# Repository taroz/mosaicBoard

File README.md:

# mosaic-Board
## Introduction
- **mosaic-Board** = [**mosaic**](https://github.com/septentrio-gnss/mosaicHAT) + **micro SD card** + **Ethernet** + **Case**
- We use [Septentrio's mosaic-X5](https://www.septentrio.com/en/products/gnss-receivers/rover-base-receivers/receivers-module/mosaic) GNSS module which is a **low-cost** and **survey-grade** GNSS receiver
- This project is inspired by [mosaicHAT](https://github.com/septentrio-gnss/mosaicHAT) and extends it further. Thanks to the wonderful project [mosaicHAT](https://github.com/septentrio-gnss/mosaicHAT)!
- License: [Creative Commons Attribution Share-Alike License](https://creativecommons.org/licenses/by-sa/4.0/). and [Open Source HW](https://www.oshwa.org/definition/)  

## Features
- The mosaic-Board has a RJ45 LAN connector and can easily distribute GNSS reference station data over the Internet without a PC by using mosaic's built-in Ntrip Caster or Ntrip Server.
- The micro SD card enables use as a GNSS logger without a PC.

## Board
- The design of the board is based on the original [mosaicHAT](https://github.com/septentrio-gnss/mosaicHAT).
  - RJ45 connector has been added
  - Micro SD card and log button have been added for data logging capability
- [KiCAD files](./board/KiCAD) and [gerber](./board/gerber)
- Bill of Materials (BOM) is [here](./board/BOM.xlsx)                                 

## Case
- Metal case design data (Fusion 360, STEP) is [available](./case)

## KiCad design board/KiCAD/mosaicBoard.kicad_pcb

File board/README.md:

# mosaic-Board Design Files
- We used KiCAD 6 for our design. [KiCAD 6 or later](https://www.kicad.org/) must be installed in order to edit the design data.
- BOM
  - `BOM.xlsx` shows the parts to be used and where to obtain them.

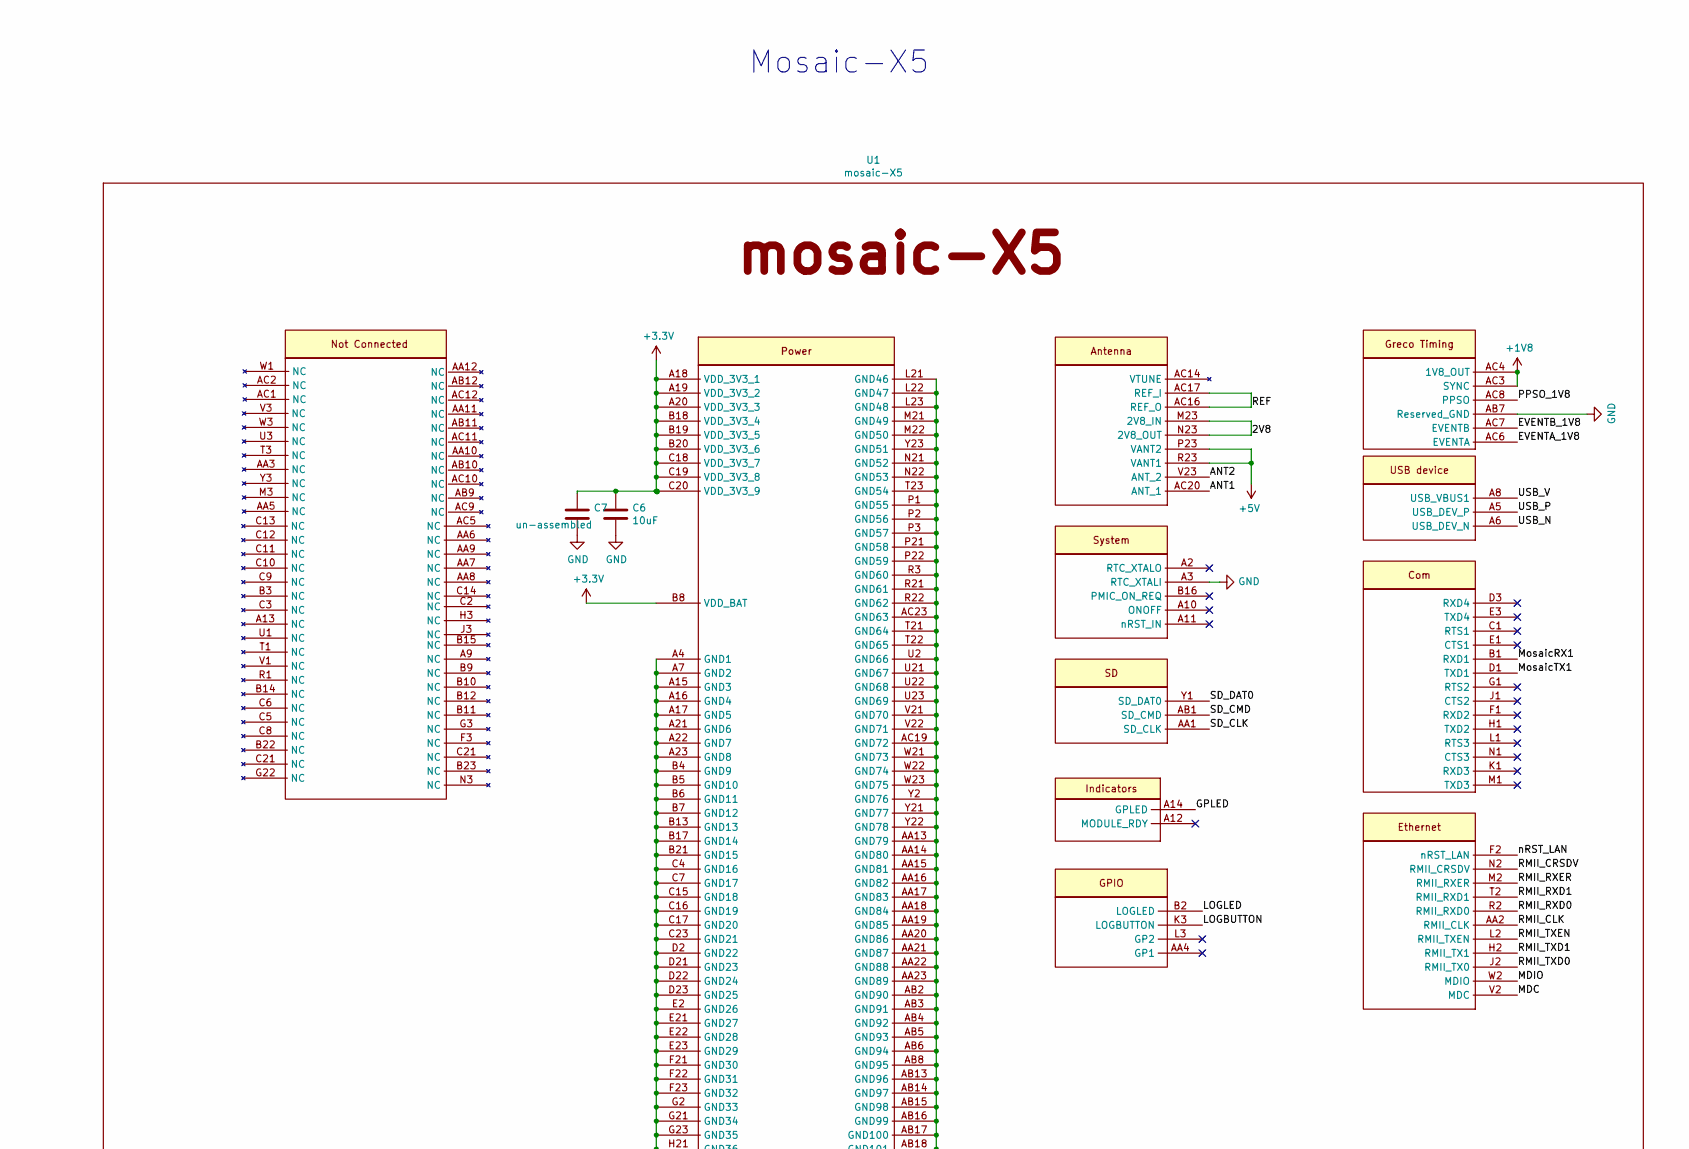
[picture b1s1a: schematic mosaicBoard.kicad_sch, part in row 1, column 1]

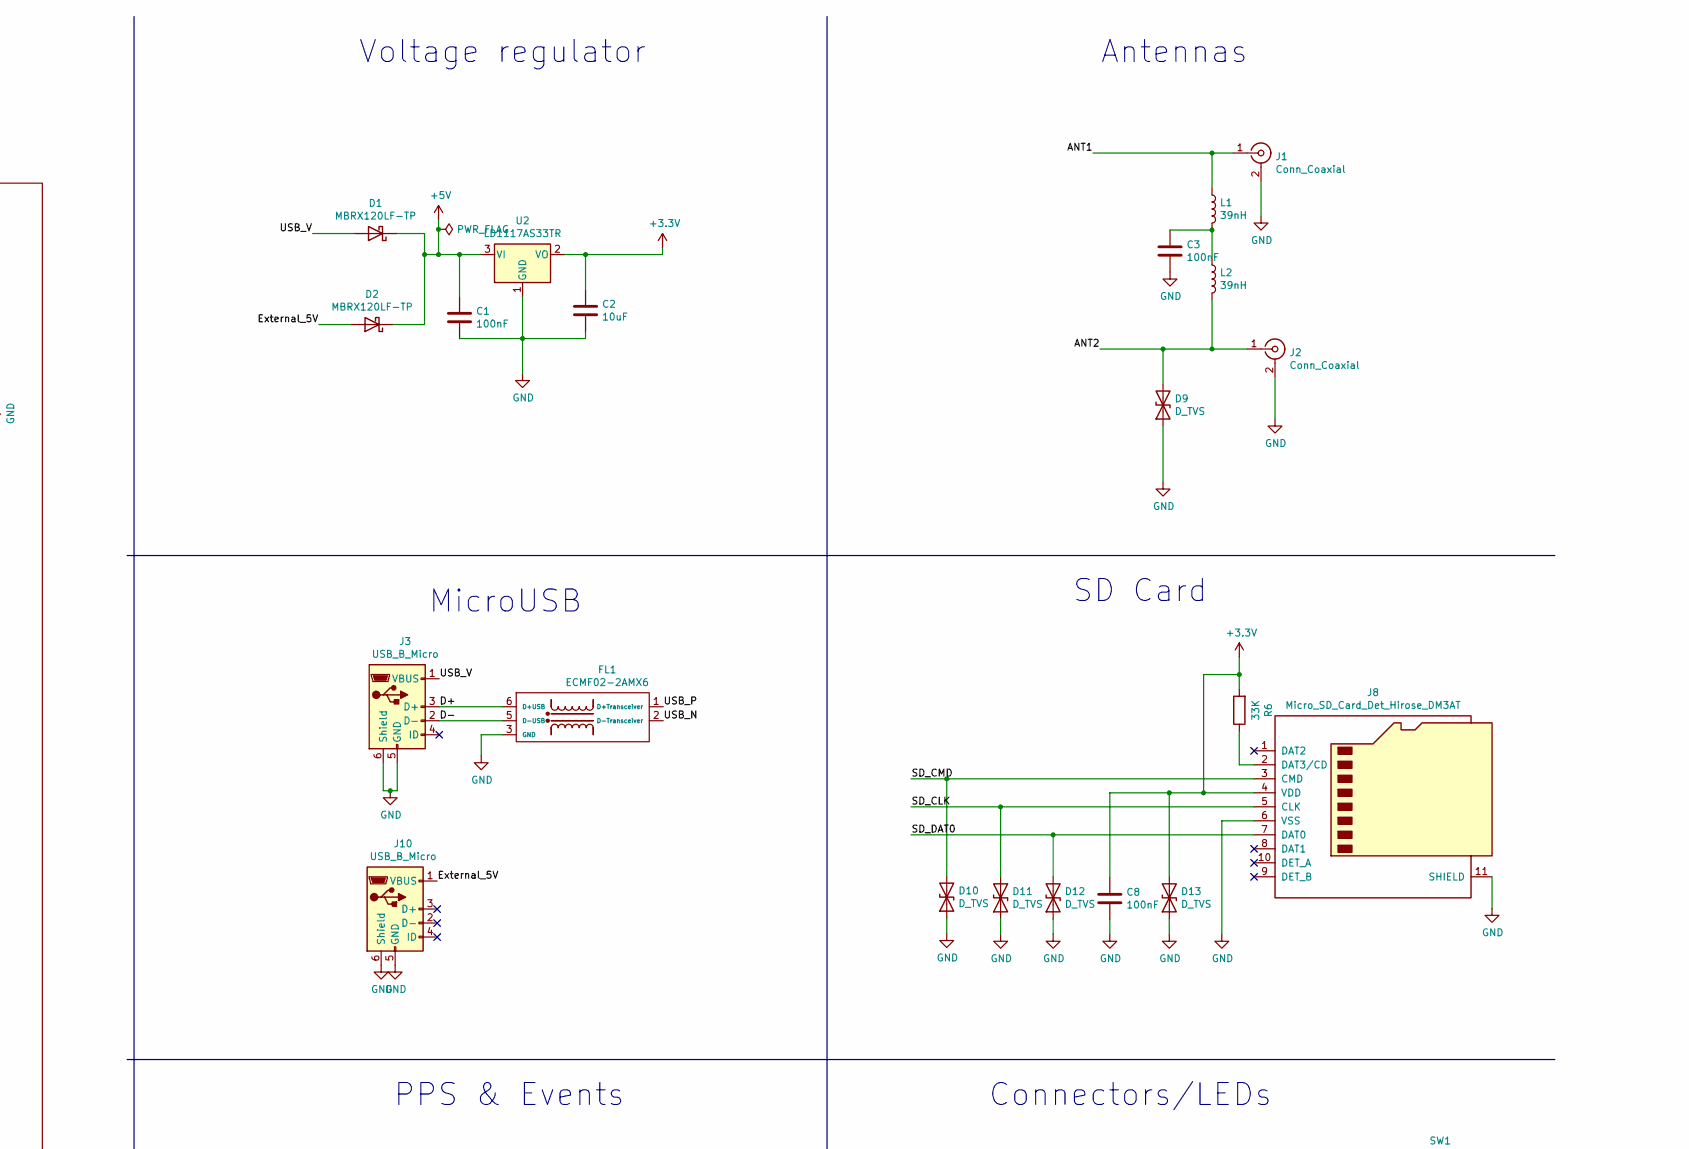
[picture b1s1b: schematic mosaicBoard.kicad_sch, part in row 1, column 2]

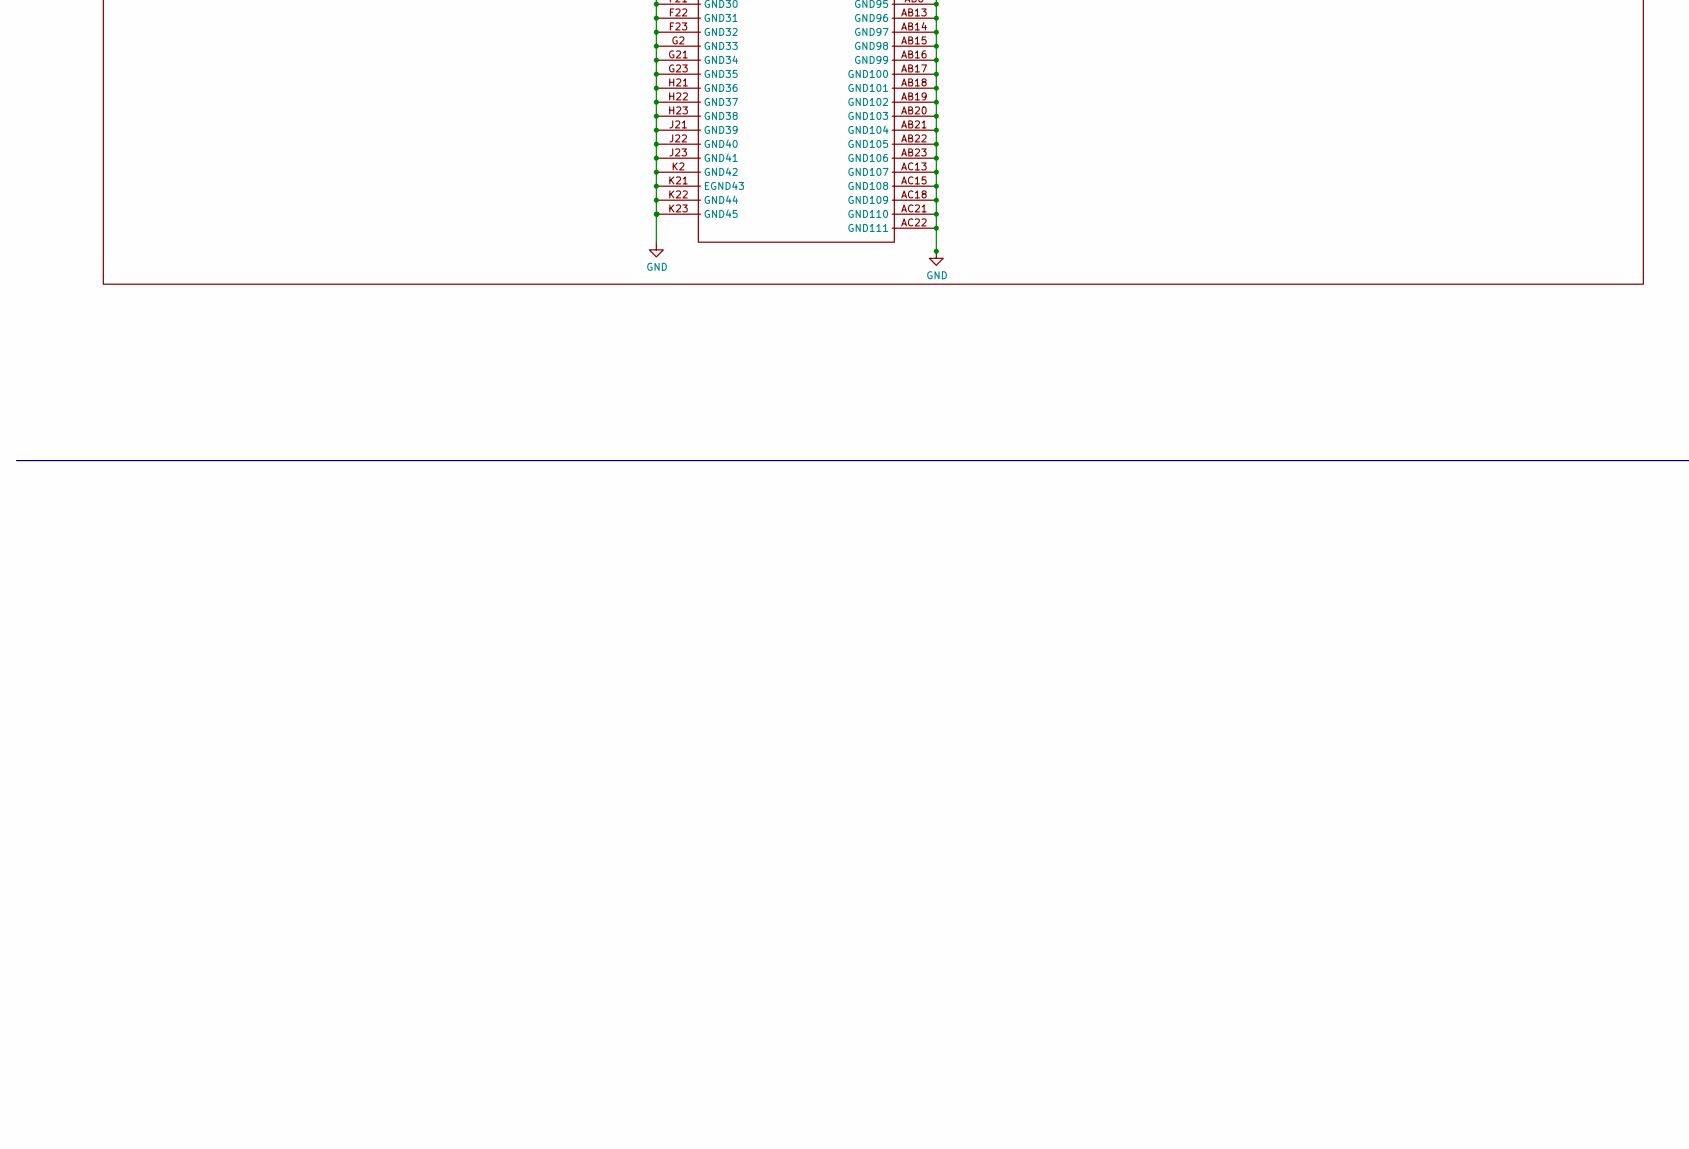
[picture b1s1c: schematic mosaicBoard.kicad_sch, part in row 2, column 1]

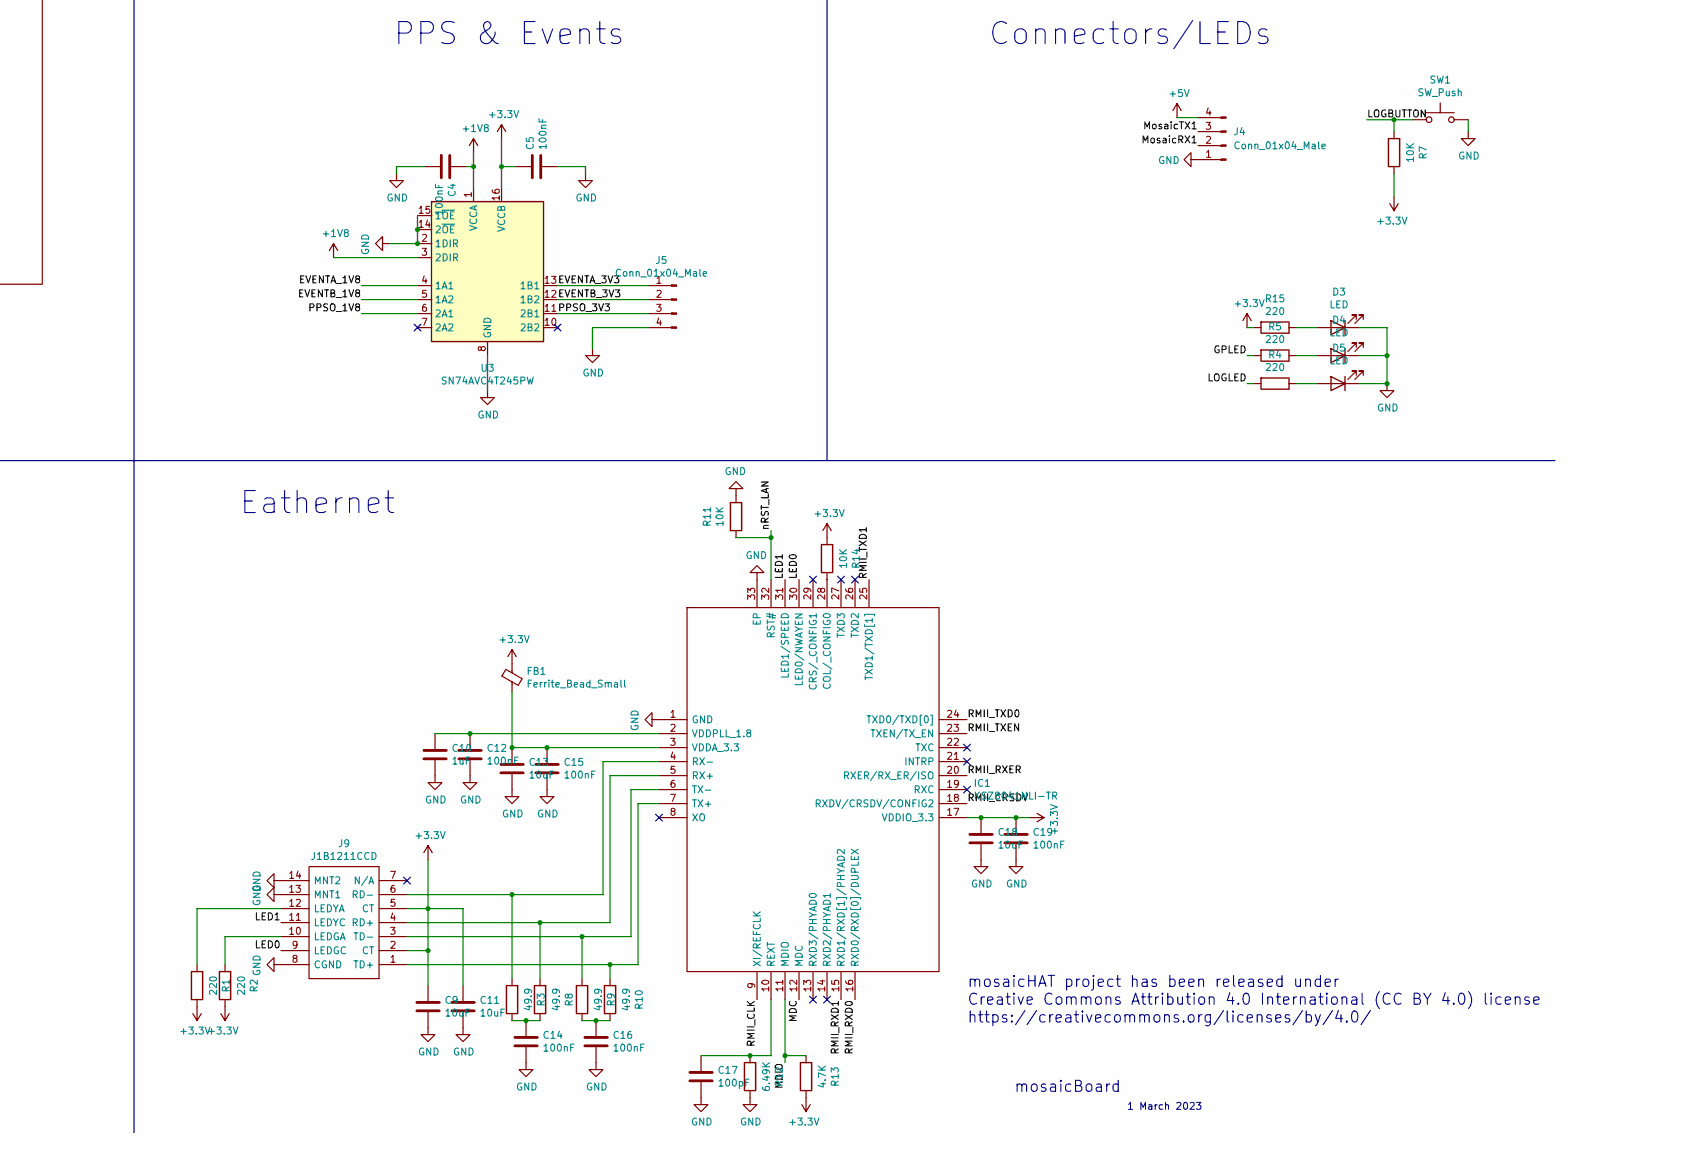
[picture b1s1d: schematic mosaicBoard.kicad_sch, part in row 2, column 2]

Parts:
C1, C3, C4, C5, C8, C12, C14, C15, C16, C19: 100nF; C_0603_1608Metric
C2, C6, C9, C11, C13, C18: 10uF; C_0603_1608Metric
C7: un-assembled; C_0603_1608Metric
C10: 1uF; C_0603_1608Metric
C17: 100pF; C_0603_1608Metric
D1, D2: MBRX120LF-TP; D_SOD-123
D3: LED; LED_D1.8mm_W1.8mm_H2.4mm_Horizontal_O1.27mm_Z1.6mm
D4: LED; LED_D1.8mm_W1.8mm_H2.4mm_Horizontal_O3.81mm_Z4.9mm
D5: LED; LED_D1.8mm_W1.8mm_H2.4mm_Horizontal_O6.35mm_Z8.2mm
D9, D10, D11, D12, D13: D_TVS; R_0402_1005Metric
FB1: Ferrite_Bead_Small; L_0603_1608Metric
FL1: ECMF02-2AMX6; ST_UQFN-6L_1.5x1.7mm_Pitch0.5mm
IC1: KSZ8041NLI-TR; QFN50P500X500X90-33N-D; Mouser Part Number 998-KSZ8041NLITR
J1, J2: Conn_Coaxial; SMA_Amphenol_132203-12_Horizontal_mod
J3, J10: USB_B_Micro; USB_Micro-B_Molex-105017-0001
J4, J5: Conn_01x04_Male; PinHeader_1x04_P2.54mm_Vertical
J8: Micro_SD_Card_Det_Hirose_DM3AT; microSD_HC_Hirose_DM3AT-SF-PEJM5
J9: J1B1211CCD; Mouser Part Number 950-J1B1211CCD
L1, L2: 39nH; L_0603_1608Metric
R1, R2, R4, R5, R15: 220; R_0603_1608Metric
R3, R8, R9, R10: 49.9; R_0603_1608Metric
R6: 33K; R_0603_1608Metric
R7, R11, R14: 10K; R_0603_1608Metric
R12: 6.49K; R_0603_1608Metric
R13: 4.7K; R_0603_1608Metric
SW1: SW_Push; SW_Tactile_SKHH_Angled
U1: mosaic-X5; mosaic_X5
U2: LD1117AS33TR; SOT-223
U3: SN74AVC4T245PW; TSSOP-16_4.4x5mm_P0.65mm

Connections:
+1V8: C4.1, U1.AC3 (SYNC), U1.AC4 (1V8_OUT), U3.1 (VCCA), U3.3 (2DIR)
+3.3V: C2.1, C5.1, C6.1, C7.1, C8.1, C9.1, C11.1, C18.1, C19.1, D13.2 (A2), FB1.1, IC1.17 (VDDIO_3.3), J8.4 (VDD), J9.2 (CT), J9.5 (CT), R1.1, R2.1, R6.2, R7.1, R13.1, R14.2, R15.2, U1.A18 (VDD_3V3_1), U1.A19 (VDD_3V3_2), U1.A20 (VDD_3V3_3), U1.B8 (VDD_BAT), U1.B18 (VDD_3V3_4), U1.B19 (VDD_3V3_5), U1.B20 (VDD_3V3_6), U1.C18 (VDD_3V3_7), U1.C19 (VDD_3V3_8), U1.C20 (VDD_3V3_9), U2.2 (VO), U3.16 (VCCB)
+5V: C1.1, D1.1 (K), D2.1 (K), J4.4, U1.P23 (VANT2), U1.R23 (VANT1), U2.3 (VI)
/2V8: U1.M23 (2V8_IN), U1.N23 (2V8_OUT)
/ANT1: J1.1 (In), L1.1, U1.AC20 (ANT_1)
/ANT2: D9.2 (A2), J2.1 (In), L2.2, U1.V23 (ANT_2)
/D+: FL1.6 (D+USB), J3.3 (D+)
/D-: FL1.5 (D-USB), J3.2 (D-)
/EVENTA_1V8: U1.AC6 (EVENTA), U3.4 (1A1)
/EVENTA_3V3: J5.1, U3.13 (1B1)
/EVENTB_1V8: U1.AC7 (EVENTB), U3.5 (1A2)
/EVENTB_3V3: J5.2, U3.12 (1B2)
/External_5V: D2.2 (A), J10.1 (VBUS)
/GPLED: R5.2, U1.A14 (GPLED)
/LED0: IC1.30 (LED0/NWAYEN), J9.9 (LEDGC)
/LED1: IC1.31 (LED1/SPEED), J9.11 (LEDYC)
/LOGBUTTON: R7.2, SW1.1, U1.K3 (LOGBUTTON)
/LOGLED: R4.2, U1.B2 (LOGLED)
/MDC: IC1.12 (MDC), U1.V2 (MDC)
/MDIO: IC1.11 (MDIO), R13.2, U1.W2 (MDIO)
/MosaicRX1: J4.2, U1.B1 (RXD1)
/MosaicTX1: J4.3, U1.D1 (TXD1)
/PPSO_1V8: U1.AC8 (PPSO), U3.6 (2A1)
/PPSO_3V3: J5.3, U3.11 (2B1)
/REF: U1.AC16 (REF_O), U1.AC17 (REF_I)
/RMII_CLK: IC1.9 (XI/REFCLK), U1.AA2 (RMII_CLK)
/RMII_CRSDV: IC1.18 (RXDV/CRSDV/CONFIG2), U1.N2 (RMII_CRSDV)
/RMII_RXD0: IC1.16 (RXD0/RXD[0]/DUPLEX), U1.R2 (RMII_RXD0)
/RMII_RXD1: IC1.15 (RXD1/RXD[1]/PHYAD2), U1.T2 (RMII_RXD1)
/RMII_RXER: IC1.20 (RXER/RX_ER/ISO), U1.M2 (RMII_RXER)
/RMII_TXD0: IC1.24 (TXD0/TXD[0]), U1.J2 (RMII_TX0)
/RMII_TXD1: IC1.25 (TXD1/TXD[1]), U1.H2 (RMII_TX1)
/RMII_TXEN: IC1.23 (TXEN/TX_EN), U1.L2 (RMII_TXEN)
/SD_CLK: D11.2 (A2), J8.5 (CLK), U1.AA1 (SD_CLK)
/SD_CMD: D10.2 (A2), J8.3 (CMD), U1.AB1 (SD_CMD)
/SD_DAT0: D12.2 (A2), J8.7 (DAT0), U1.Y1 (SD_DAT0)
/USB_N: FL1.2 (D-Transceiver), U1.A6 (USB_DEV_N)
/USB_P: FL1.1 (D+Transceiver), U1.A5 (USB_DEV_P)
/USB_V: D1.2 (A), J3.1 (VBUS), U1.A8 (USB_VBUS1)
/nRST_LAN: IC1.32 (RST#), R11.2, U1.F2 (nRST_LAN)
GND: C1.2, C2.2, C3.2, C4.2, C5.2, C6.2, C7.2, C8.2, C9.2, C10.2, C11.2, C12.2, C13.2, C14.2, C15.2, C16.2, C17.2, C18.2, C19.2, D3.1 (K), D4.1 (K), D5.1 (K), D9.1 (A1), D10.1 (A1), D11.1 (A1), D12.1 (A1), D13.1 (A1), FL1.3 (GND), IC1.1 (GND), IC1.33 (EP), J1.2 (Ext), J2.2 (Ext), J3.5 (GND), J3.6 (Shield), J4.1, J5.4, J8.6 (VSS), J8.11 (SHIELD), J9.8 (CGND), J9.13 (MNT1), J9.14 (MNT2), J10.5 (GND), J10.6 (Shield), R11.1, R12.1, SW1.2, U1.A3 (RTC_XTALI), U1.A4 (GND1), U1.A7 (GND2), U1.A15 (GND3), U1.A16 (GND4), U1.A17 (GND5), U1.A21 (GND6), U1.A22 (GND7), U1.A23 (GND8), U1.AA13 (GND79), U1.AA14 (GND80), U1.AA15 (GND81), U1.AA16 (GND82), U1.AA17 (GND83), U1.AA18 (GND84), U1.AA19 (GND85), U1.AA20 (GND86), U1.AA21 (GND87), U1.AA22 (GND88), U1.AA23 (GND89), U1.AB2 (GND90), U1.AB3 (GND91), U1.AB4 (GND92), U1.AB5 (GND93), U1.AB6 (GND94), U1.AB7 (Reserved_GND), U1.AB8 (GND95), U1.AB13 (GND96), U1.AB14 (GND97), U1.AB15 (GND98), U1.AB16 (GND99), U1.AB17 (GND100), U1.AB18 (GND101), U1.AB19 (GND102), U1.AB20 (GND103), U1.AB21 (GND104), U1.AB22 (GND105), U1.AB23 (GND106), U1.AC13 (GND107), U1.AC15 (GND108), U1.AC18 (GND109), U1.AC19 (GND72), U1.AC21 (GND110), U1.AC22 (GND111), U1.AC23 (GND63), U1.B4 (GND9), U1.B5 (GND10), U1.B6 (GND11), U1.B7 (GND12), U1.B13 (GND13), U1.B17 (GND14), U1.B21 (GND15), U1.C4 (GND16), U1.C7 (GND17), U1.C15 (GND18), U1.C16 (GND19), U1.C17 (GND20), U1.C23 (GND21), U1.D2 (GND22), U1.D21 (GND23), U1.D22 (GND24), U1.D23 (GND25), U1.E2 (GND26), U1.E21 (GND27), U1.E22 (GND28), U1.E23 (GND29), U1.F21 (GND30), U1.F22 (GND31), U1.F23 (GND32), U1.G2 (GND33), U1.G21 (GND34), U1.G23 (GND35), U1.H21 (GND36), U1.H22 (GND37), U1.H23 (GND38), U1.J21 (GND39), U1.J22 (GND40), U1.J23 (GND41), U1.K2 (GND42), U1.K21 (EGND43), U1.K22 (GND44), U1.K23 (GND45), U1.L21 (GND46), U1.L22 (GND47), U1.L23 (GND48), U1.M21 (GND49), U1.M22 (GND50), U1.N21 (GND52), U1.N22 (GND53), U1.P1 (GND55), U1.P2 (GND56), U1.P3 (GND57), U1.P21 (GND58), U1.P22 (GND59), U1.R3 (GND60), U1.R21 (GND61), U1.R22 (GND62), U1.T21 (GND64), U1.T22 (GND65), U1.T23 (GND54), U1.U2 (GND66), U1.U21 (GND67), U1.U22 (GND68), U1.U23 (GND69), U1.V21 (GND70), U1.V22 (GND71), U1.W21 (GND73), U1.W22 (GND74), U1.W23 (GND75), U1.Y2 (GND76), U1.Y21 (GND77), U1.Y22 (GND78), U1.Y23 (GND51), U2.1 (GND), U3.2 (1DIR), U3.8 (GND), U3.9 (GND), U3.14 (2~OE), U3.15 (1~OE)
unnamed: C3.1, L1.2, L2.1
unnamed: C10.1, C12.1, IC1.2 (VDDPLL_1.8)
unnamed: C13.1, C15.1, FB1.2, IC1.3 (VDDA_3.3)
unnamed: C14.1, R3.1, R8.1
unnamed: C16.1, R9.1, R10.1
unnamed: C17.1, IC1.10 (REXT), R12.2
unnamed: D3.2 (A), R15.1
unnamed: D4.2 (A), R5.1
unnamed: D5.2 (A), R4.1
unnamed: IC1.4 (RX-), J9.6 (RD-), R3.2
unnamed: IC1.5 (RX+), J9.4 (RD+), R8.2
unnamed: IC1.6 (TX-), J9.3 (TD-), R9.2
unnamed: IC1.7 (TX+), J9.1 (TD+), R10.2
unnamed: IC1.28 (COL/_CONFIG0), R14.1
unnamed: J8.2 (DAT3/CD), R6.1
unnamed: J9.10 (LEDGA), R2.2
unnamed: J9.12 (LEDYA), R1.2

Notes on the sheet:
mosaicHAT project has been released under Creative Commons Attribution 4.0 International (CC BY 4.0) license https://creativecommons.org/licenses/by/4.0/
SD Card
1 March 2023
Eathernet
Voltage regulator
PPS & Events
Mosaic-X5
Antennas
mosaicBoard
Connectors/LEDs
MicroUSB

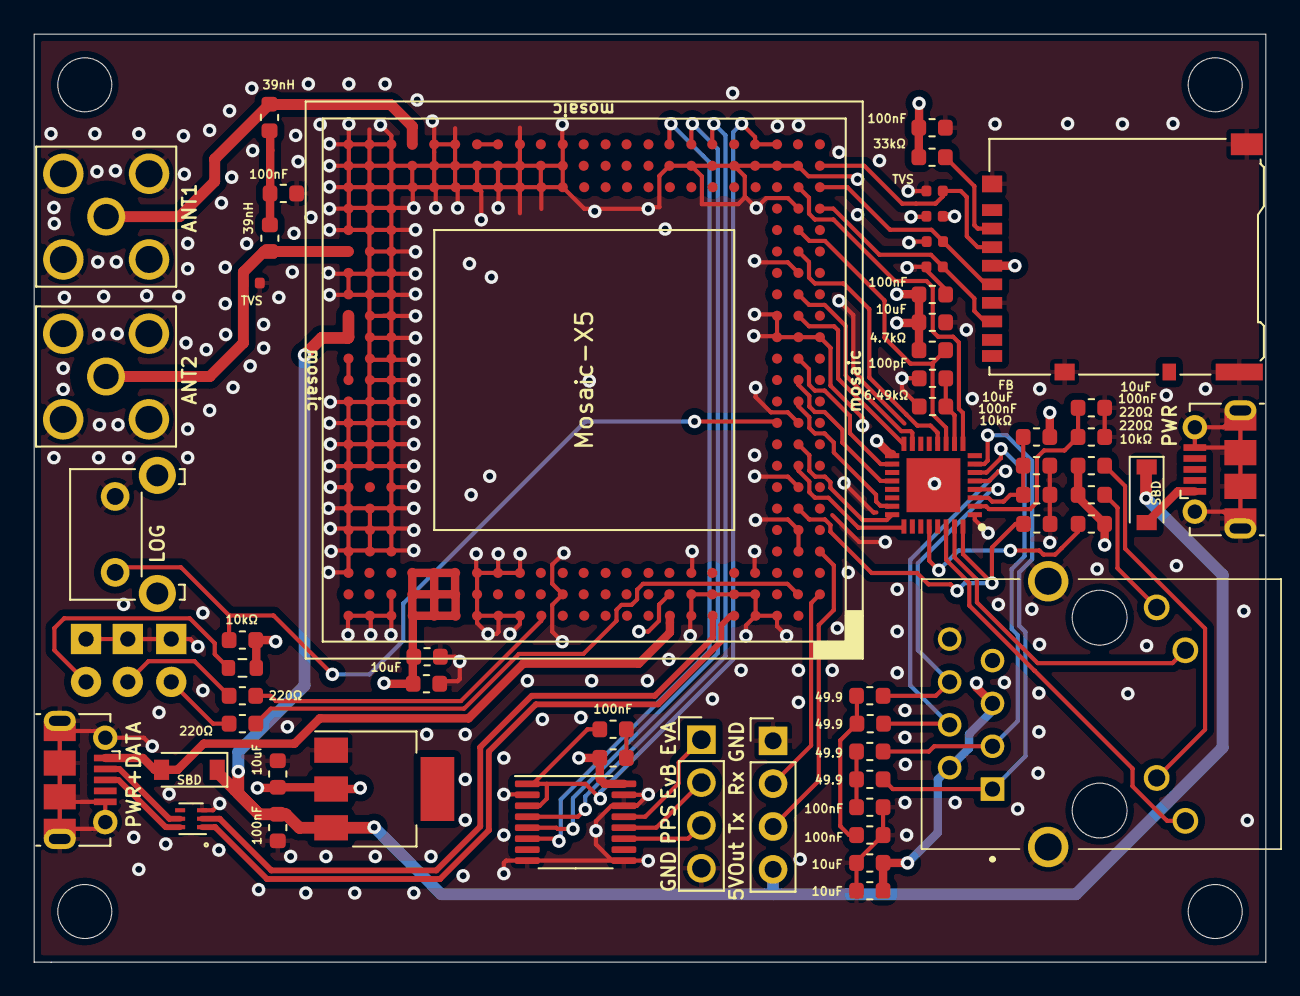
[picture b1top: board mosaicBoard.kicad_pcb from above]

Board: 4 copper layers, 73.0 x 55.0 mm, 61 parts (0 on the bottom side), 58 nets.

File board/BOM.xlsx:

Designator | Footprint | Quantity | Value | MPN
C1, C12, C14, C15, C16, C19, C3, C4, C5, C8 | C_0603_1608Metric | 10 | 100nF
C10 | C_0603_1608Metric | 1 | 1uF
C11, C13, C18, C2, C6, C9 | C_0603_1608Metric | 6 | 10uF
C17 | C_0603_1608Metric | 1 | 100pF
C7 | C_0603_1608Metric | 1 | un-assembled
D1, D2 | D_SOD-123 | 2 | MBRX120LF-TP | MBRX120LF-TP | https://www.digikey.com/product-detail/en/micro-commercial-c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
D10, D11, D12, D13, D9 | R_0402_1005Metric | 5 | D_TVS | SESD0402X1BN-0010-098 | https://www.digikey.com/en/products/detail/littelfuse-inc/SE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
D3 | LED_D1.8mm_W1.8mm_H2.4mm_Horizontal_O1.27mm_Z1.6mm | 1 | LED | TLUG2401 | https://www.digikey.com/en/products/detail/vishay-semiconduc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
D4 | LED_D1.8mm_W1.8mm_H2.4mm_Horizontal_O3.81mm_Z4.9mm | 1 | LED | TLUG2401 | https://www.digikey.com/en/products/detail/vishay-semiconduc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
D5 | LED_D1.8mm_W1.8mm_H2.4mm_Horizontal_O6.35mm_Z8.2mm | 1 | LED | TLUG2401 | https://www.digikey.com/en/products/detail/vishay-semiconduc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
FB1 | L_0603_1608Metric | 1 | Ferrite_Bead_Small | BLM18RK601SN1D | https://www.digikey.com/en/products/detail/murata-electronic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
FL1 | ST_UQFN-6L_1.5x1.7mm_Pitch0.5mm | 1 | ECMF02-2AMX6 | ECMF02-2AMX6 | https://www.digikey.com/en/products/detail/stmicroelectronic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
IC1 | QFN50P500X500X90-33N-D | 1 | KSZ8041NLI-TR | KSZ8041NLI-TR | https://www.digikey.com/en/products/detail/microchip-technol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
J1, J2 | SMA_Amphenol_132203-12_Horizontal_mod | 2 | Conn_Coaxial | 132136 | https://www.digikey.com/en/products/detail/amphenol-rf/13213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
J10, J3 | USB_Micro-B_Molex-105017-0001 | 2 | USB_B_Micro | 1050170001 | https://www.digikey.com/en/products/detail/molex/1050170001/2350832
J4, J5 | PinHeader_1x04_P2.54mm_Vertical | 2 | Conn_01x04_Male
J8 | microSD_HC_Hirose_DM3AT-SF-PEJM5 | 1 | Micro_SD_Card | DM3AT-SF-PEJM5 | https://www.digikey.com/en/products/detail/hirose-electric-c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
J9 | J1B1211CCD | 1 | J1B1211CCD | J1B1211CCD | https://www.digikey.com/en/products/detail/wiznet/J1B1211CCD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
L1, L2 | L_0603_1608Metric | 2 | 39nH
R1, R15, R2, R4, R5 | R_0603_1608Metric | 5 | 220
R10, R3, R8, R9 | R_0603_1608Metric | 4 | 49.9
R11, R14, R7 | R_0603_1608Metric | 3 | 10K
R12 | R_0603_1608Metric | 1 | 6.49K
R13 | R_0603_1608Metric | 1 | 4.7K
R6 | R_0603_1608Metric | 1 | 33K
SW1 | SW_Tactile_SKHH_Angled | 1 | SW_Push | SKHHLQA010 | https://www.mouser.com/ProductDetail/Alps-Alpine/SKHHLQA010
U1 | mosaic_X5 | 1 | mosaic-X5 | 410322 | https://www.digikey.com/en/products/detail/septentrio-inc/41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
U2 | SOT-223 | 1 | LD1117AS33TR | LD1117AS33TR | https://www.digikey.com/product-detail/en/stmicroelectronics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
U3 | TSSOP-16_4.4x5mm_P0.65mm | 1 | SN74AVC4T245PW | SN74AVC4T245PWR | https://www.digikey.com/product-detail/en/texas-instruments/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
Case |  | 1 | TAKACHI | EXEF7-3-9 | https://www.takachi-enclosure.com/products/EXEF

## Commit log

2023-03-07 Add mosaicBoard project
